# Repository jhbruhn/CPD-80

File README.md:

# Crazy Programmable Device (CPD)

## (Planned) Features

* 6MHz Z80 Processor
* UART Serial Communication
* 64k RAM
* 32k ROM
* CF Card Support (FAT16 or FAT12)

## Memory layout:
| Address       | Type |
| ------------- | ------------- |
| 0x0000-0x7FFF | ROM / RAM  |
| 0x8000-0xFFFF | RAM  |

## IO

| A11| A10| A9 | A8 | Device                                                  |
| ---|----|----|----|---------------------------------------------------------|
| 0  | 0  | 0  | 0  | IDE Port (CF Card)                                      |
| 0  | 0  | 0  | 1  | UART (16550)                                            |
| 0  | 0  | 1  | 0  | PS/2 Keyboard                                           |
| 0  | 0  | 1  | 1  | RTC-72421                                               |
| 0  | 1  | 0  | 0  | MemoryBank (write 0 for ROM and 2 for RAM in first 32k) |
| 0  | 1  | 0  | 1  | Video (TMS9918)                                         |
| 0  | 1  | 1  | 0  | Audio (AY-3-8910A)                                      |

To Address device 0:

B = 0

OUT (C), d

To Address device 1:

B = 1

OUT (C), d

etc...

sdcc:
__banked __ad(0x16c) int pedabaumert oder so

##Future:
Video Card with TMS9918. Also PS/2 keyboard input (or something similar). Real time Clock?

## Boot:
* start at 0x0000.
* load Bootsector from CF card to 0x8000, or into BANK RAM at 0x0000.
* jump to 0x8000 (0x0000)
* Bootsector loads FAT files, executes KERNEL.ULF or something like that. Autoexec.

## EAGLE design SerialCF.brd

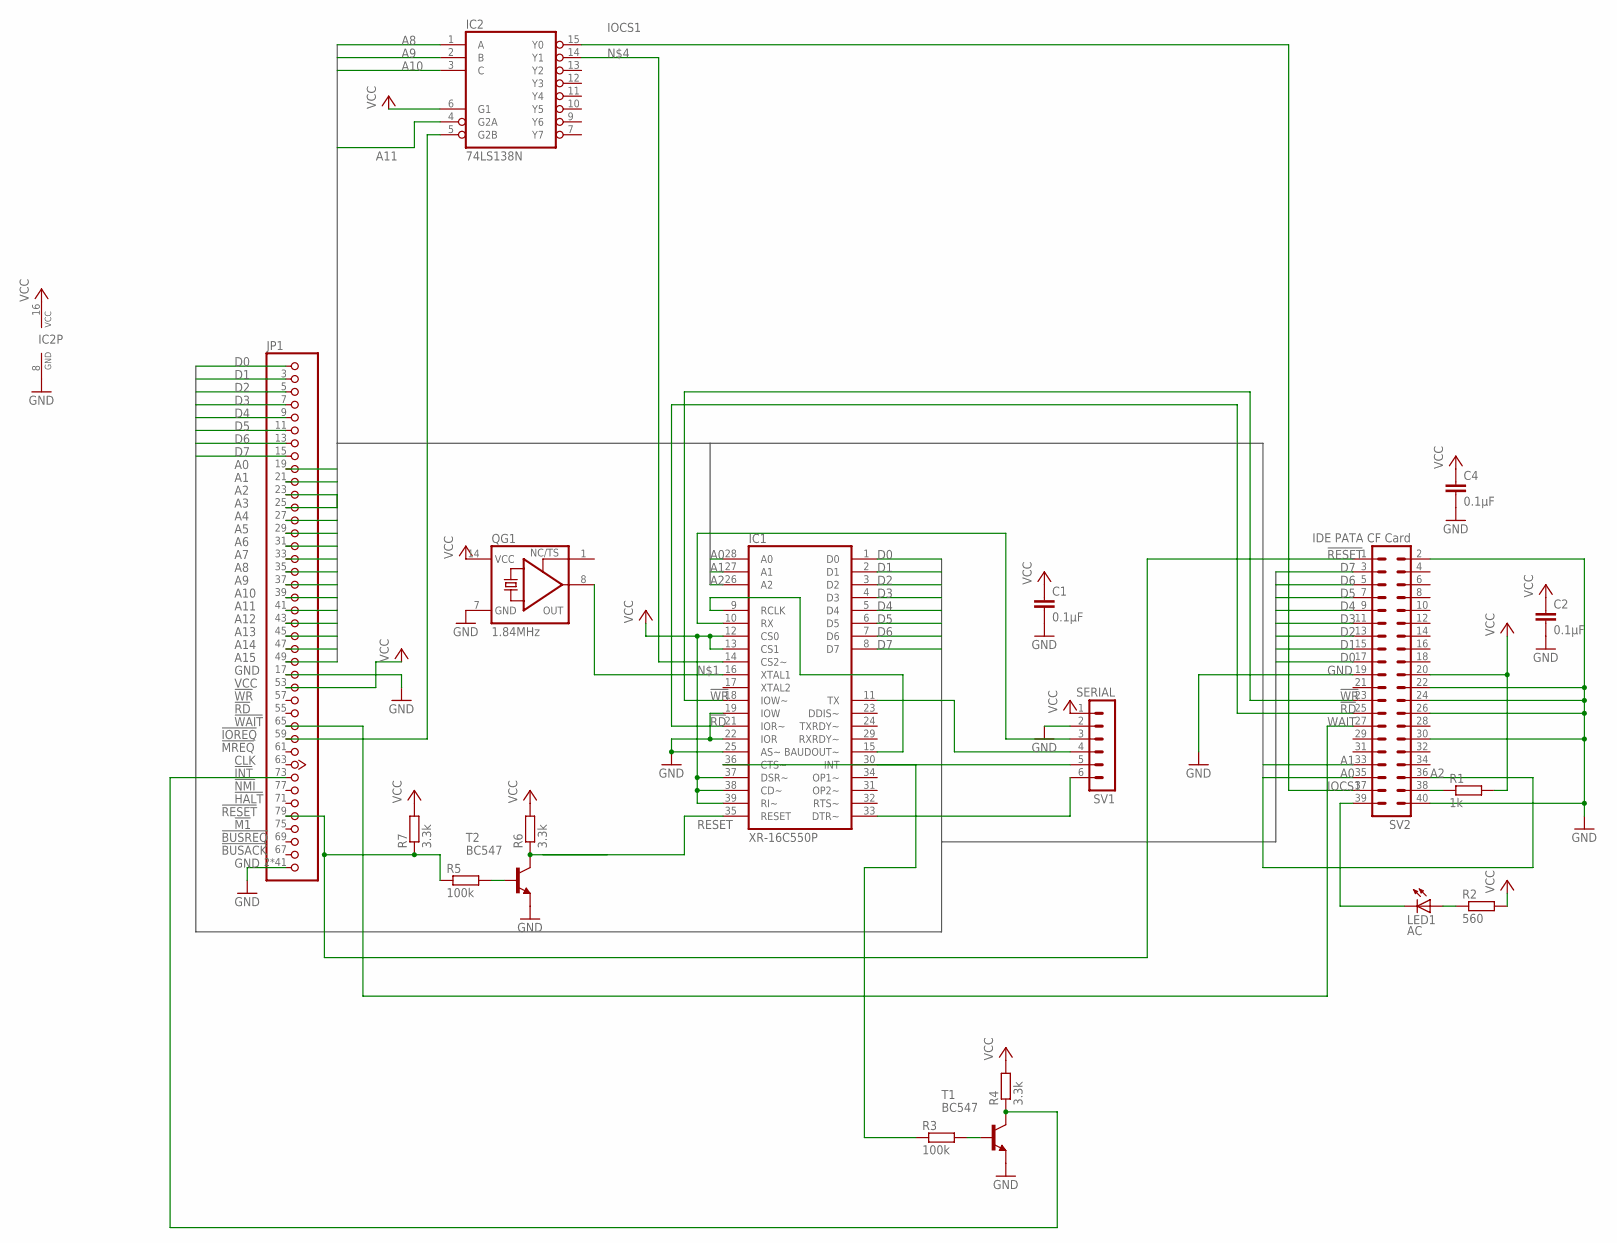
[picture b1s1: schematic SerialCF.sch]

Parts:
C1, C2, C4: 0.1µF; C5B2.5
IC1: XR-16C550P; DIL40
IC2: 74LS138N; DIL16
JP1: JEANNECTOR/90; 2X25/90
LED1: AC; LED5MM
QG1: 1.84MHz; DIL14S
R1: 1k; 0207/10; MPN MCRE000037
R2: 560; 0204/7
R3, R5: 100k; 0207/2V
R4, R6, R7: 3.3k; 0207/2V
SV1: SERIAL; MA06-1
SV2: IDE PATA CF Card; MA20-2
T1, T2: BC547; TO92

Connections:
!RD: IC1.21 (IOR~), SV2.25
!RESET: JP1.79 (!RESET), R7.1, SV2.1
!WR: IC1.18 (IOW~), SV2.23
A0: IC1.28 (A0), JP1.19 (A0), SV2.35
A1: IC1.27 (A1), JP1.21 (A1), SV2.33
A2: IC1.26 (A2), JP1.23 (A2), SV2.36
A3: JP1.25 (A3)
A4: JP1.27 (A4)
A5: JP1.29 (A5)
A6: JP1.31 (A6)
A7: JP1.33 (A7)
A8: IC2.1 (A), JP1.35 (A8)
A9: IC2.2 (B), JP1.37 (A9)
A10: IC2.3 (C), JP1.39 (A10)
A11: IC2.4 (G2A), JP1.41 (A11)
A12: JP1.43 (A12)
A13: JP1.45 (A13)
A14: JP1.47 (A14)
A15: JP1.49 (A15)
D0: IC1.1 (D0), JP1.1 (D0), SV2.17
D1: IC1.2 (D1), JP1.3 (D1), SV2.15
D2: IC1.3 (D2), JP1.5 (D2), SV2.13
D3: IC1.4 (D3), JP1.7 (D3), SV2.11
D4: IC1.5 (D4), JP1.9 (D4), SV2.9
D5: IC1.6 (D5), JP1.11 (D5), SV2.7
D6: IC1.7 (D6), JP1.13 (D6), SV2.5
D7: IC1.8 (D7), JP1.15 (D7), SV2.3
GND: C1.2, C2.2, C4.2, IC1.19 (IOW), IC1.20 (GND), IC1.22 (IOR), IC1.25 (AS~), IC2.8 (GND), JP1.2 (GND), JP1.4 (GND), JP1.6 (GND), JP1.8 (GND), JP1.10 (GND), JP1.12 (GND), JP1.14 (GND), JP1.16 (GND), JP1.17 (GND), JP1.18 (GND), JP1.20 (GND), JP1.22 (GND), JP1.24 (GND), JP1.26 (GND), JP1.28 (GND), JP1.30 (GND), JP1.32 (GND), JP1.34 (GND), JP1.36 (GND), JP1.38 (GND), JP1.40 (GND), JP1.42 (GND), JP1.44 (GND), JP1.46 (GND), JP1.48 (GND), JP1.50 (GND), JP1.51 (GND), JP1.52 (GND), JP1.54 (GND), JP1.56 (GND), JP1.58 (GND), JP1.60 (GND), JP1.62 (GND), JP1.64 (GND), JP1.66 (GND), JP1.68 (GND), JP1.70 (GND), JP1.72 (GND), JP1.74 (GND), JP1.76 (GND), JP1.78 (GND), JP1.80 (GND), QG1.7 (GND), SV1.2, SV2.2, SV2.19, SV2.22, SV2.24, SV2.26, SV2.30, SV2.40, T1.1 (E), T2.1 (E)
IOCS1: IC2.15 (Y0), SV2.37
unnamed: IC1.16 (XTAL1), QG1.8 (OUT)
unnamed: LED1.K (C), SV2.39
unnamed: LED1.A, R2.1
unnamed: IC1.14 (CS2~), IC2.14 (Y1)
unnamed: IC2.5 (G2B), JP1.59 (!IOREQ)
unnamed: R5.2, T2.2 (B)
unnamed: R6.1, T2.3 (C)
unnamed: R3.2, T1.2 (B)
unnamed: JP1.73 (!INT), R4.1, T1.3 (C)
unnamed: IC1.30 (INT), R3.1
unnamed: IC1.11 (TX), SV1.4
unnamed: IC1.36 (CTS~), SV1.5
unnamed: IC1.9 (RCLK), IC1.15 (BAUDOUT~)
unnamed: IC1.33 (DTR~), SV1.6
unnamed: IC1.10 (RX), SV1.3
unnamed: R1.1, SV2.38
RESET: IC1.35 (RESET)
VCC: C1.1, C2.1, C4.1, IC1.12 (CS0), IC1.13 (CS1), IC1.37 (DSR~), IC1.38 (CD~), IC1.39 (RI~), IC1.40 (VCC), IC2.6 (G1), IC2.16 (VCC), JP1.53 (VCC), QG1.14 (VCC), R1.2, R2.2, R4.2, R6.2, R7.2, SV1.1, SV2.20
WAIT: JP1.65 (!WAIT), SV2.27

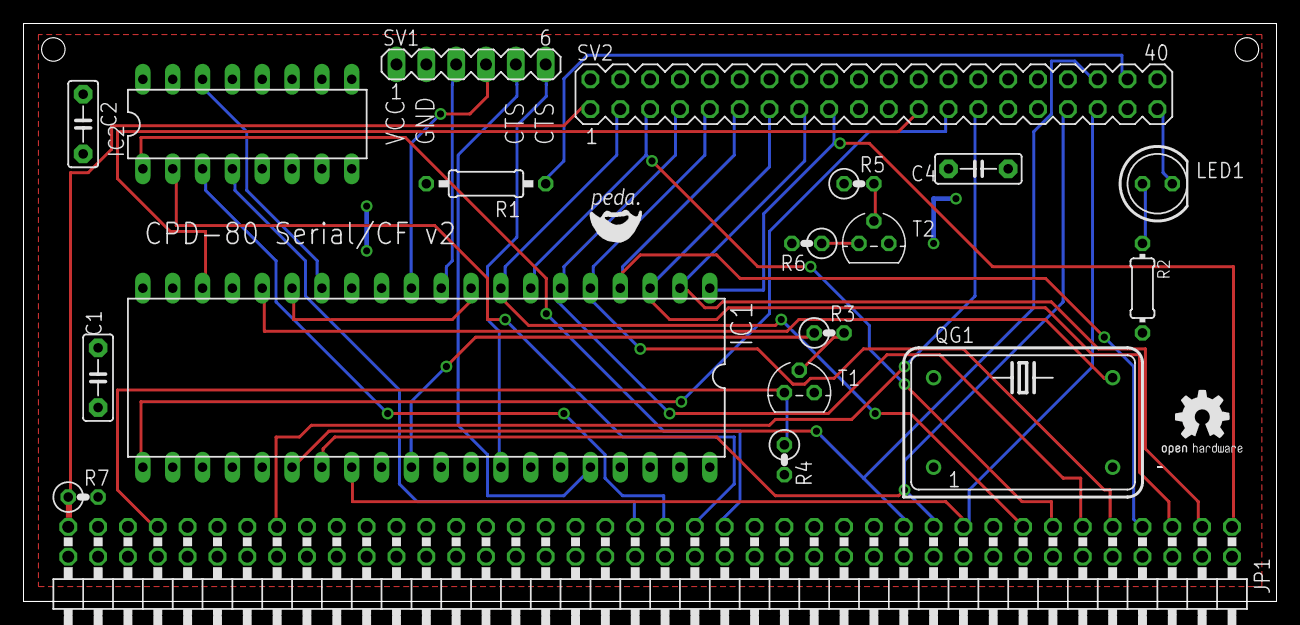
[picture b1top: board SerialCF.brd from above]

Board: 2 copper layers, 106.7 x 49.2 mm, 20 parts (0 on the bottom side), 38 nets.

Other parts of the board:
U$1: OSHW2

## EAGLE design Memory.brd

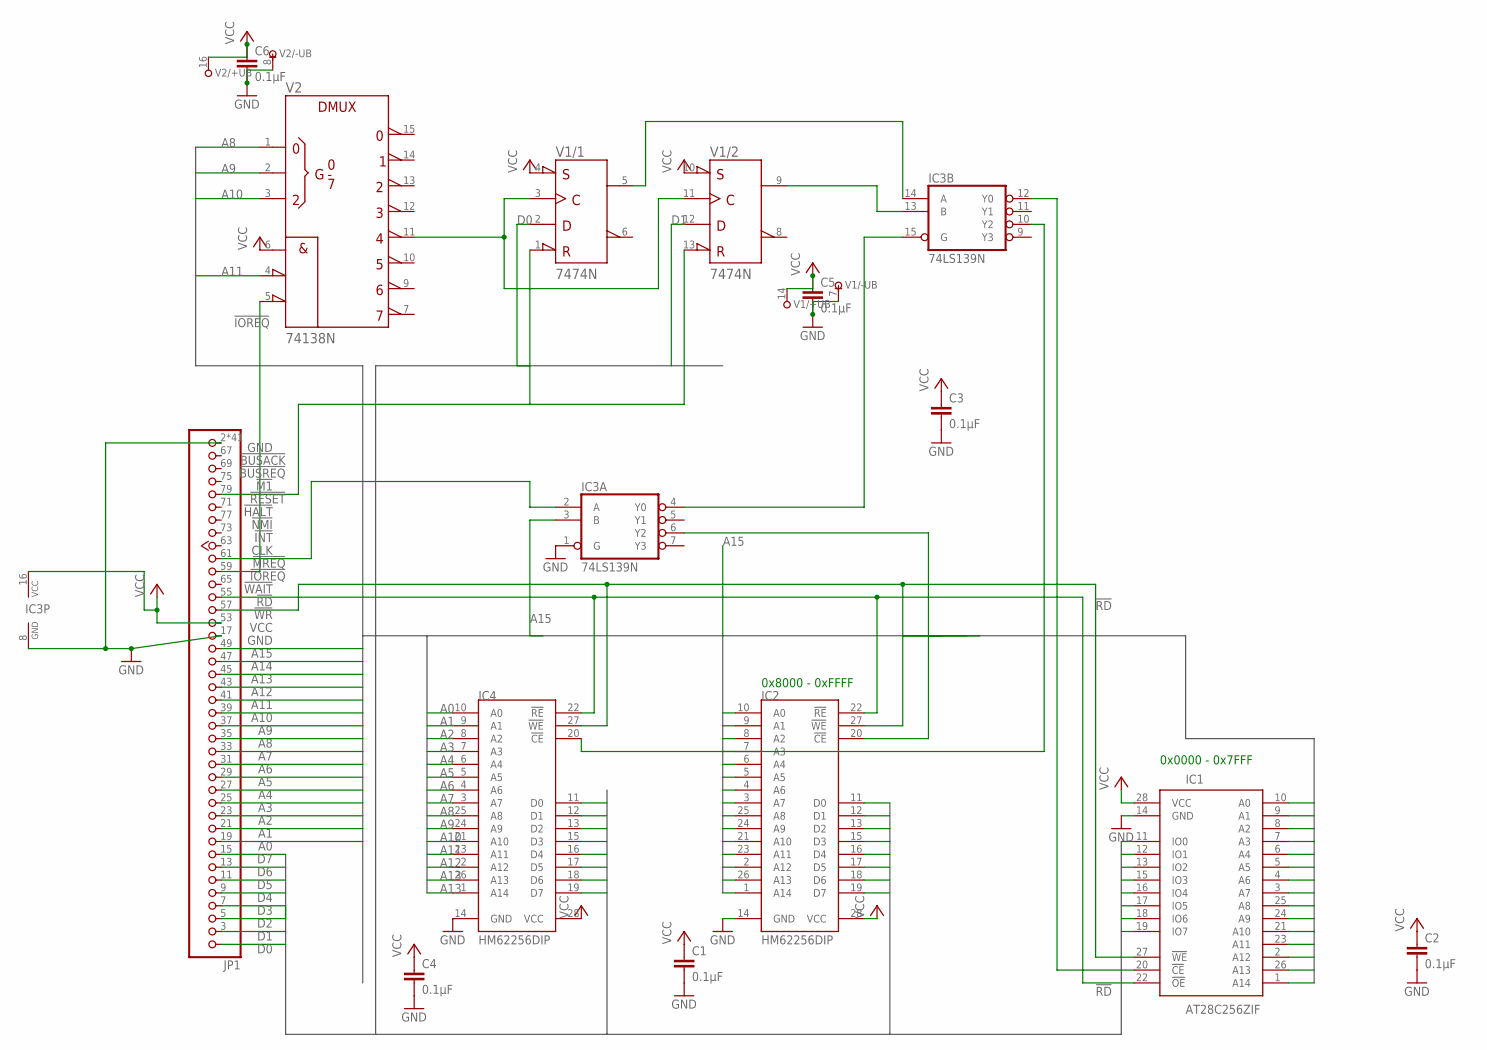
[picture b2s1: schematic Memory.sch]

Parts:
C1, C2, C3, C4, C5, C6: 0.1µF; C5B2.5
IC1: AT28C256ZIF; DIL28-ZIF
IC2, IC4: HM62256DIP; HM62256-DIP
IC3: 74LS139N; DIL16
JP1: JEANNECTOR/90; 2X25/90
V1: 7474N; DIL14
V2: 74138N; DIL16

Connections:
!IOREQ: JP1.59 (!IOREQ), V2.5 (!G2B)
!MREQ: IC3.2 (A), JP1.61 (!MREQ)
!RD: IC1.22 (!OE), IC2.22 (!RE), IC4.22 (!RE), JP1.55 (!RD)
!WR: IC1.27 (!WE), IC2.27 (!WE), IC4.27 (!WE), JP1.57 (!WR)
A0: IC1.10 (A0), IC2.10 (A0), IC4.10 (A0), JP1.19 (A0)
A1: IC1.9 (A1), IC2.9 (A1), IC4.9 (A1), JP1.21 (A1)
A2: IC1.8 (A2), IC2.8 (A2), IC4.8 (A2), JP1.23 (A2)
A3: IC1.7 (A3), IC2.7 (A3), IC4.7 (A3), JP1.25 (A3)
A4: IC1.6 (A4), IC2.6 (A4), IC4.6 (A4), JP1.27 (A4)
A5: IC1.5 (A5), IC2.5 (A5), IC4.5 (A5), JP1.29 (A5)
A6: IC1.4 (A6), IC2.4 (A6), IC4.4 (A6), JP1.31 (A6)
A7: IC1.3 (A7), IC2.3 (A7), IC4.3 (A7), JP1.33 (A7)
A8: IC1.25 (A8), IC2.25 (A8), IC4.25 (A8), JP1.35 (A8), V2.1 (A)
A9: IC1.24 (A9), IC2.24 (A9), IC4.24 (A9), JP1.37 (A9), V2.2 (B)
A10: IC1.21 (A10), IC2.21 (A10), IC4.21 (A10), JP1.39 (A10), V2.3 (C)
A11: IC1.23 (A11), IC2.23 (A11), IC4.23 (A11), JP1.41 (A11), V2.4 (!G2A)
A12: IC1.2 (A12), IC2.2 (A12), IC4.2 (A12), JP1.43 (A12)
A13: IC1.26 (A13), IC2.26 (A13), IC4.26 (A13), JP1.45 (A13)
A14: IC1.1 (A14), IC2.1 (A14), IC4.1 (A14), JP1.47 (A14)
A15: IC3.3 (B), JP1.49 (A15)
D0: IC1.11 (IO0), IC2.11 (D0), IC4.11 (D0), JP1.1 (D0), V1.2 (D)
D1: IC1.12 (IO1), IC2.12 (D1), IC4.12 (D1), JP1.3 (D1), V1.12 (D)
D2: IC1.13 (IO2), IC2.13 (D2), IC4.13 (D2), JP1.5 (D2)
D3: IC1.15 (IO3), IC2.15 (D3), IC4.15 (D3), JP1.7 (D3)
D4: IC1.16 (IO4), IC2.16 (D4), IC4.16 (D4), JP1.9 (D4)
D5: IC1.17 (IO5), IC2.17 (D5), IC4.17 (D5), JP1.11 (D5)
D6: IC1.18 (IO6), IC2.18 (D6), IC4.18 (D6), JP1.13 (D6)
D7: IC1.19 (IO7), IC2.19 (D7), IC4.19 (D7), JP1.15 (D7)
GND: C1.2, C2.2, C3.2, C4.2, C5.2, C6.2, IC1.14 (GND), IC2.14 (GND), IC3.1 (G), IC3.8 (GND), IC4.14 (GND), JP1.2 (GND), JP1.4 (GND), JP1.6 (GND), JP1.8 (GND), JP1.10 (GND), JP1.12 (GND), JP1.14 (GND), JP1.16 (GND), JP1.17 (GND), JP1.18 (GND), JP1.20 (GND), JP1.22 (GND), JP1.24 (GND), JP1.26 (GND), JP1.28 (GND), JP1.30 (GND), JP1.32 (GND), JP1.34 (GND), JP1.36 (GND), JP1.38 (GND), JP1.40 (GND), JP1.42 (GND), JP1.44 (GND), JP1.46 (GND), JP1.48 (GND), JP1.50 (GND), JP1.51 (GND), JP1.52 (GND), JP1.54 (GND), JP1.56 (GND), JP1.58 (GND), JP1.60 (GND), JP1.62 (GND), JP1.64 (GND), JP1.66 (GND), JP1.68 (GND), JP1.70 (GND), JP1.72 (GND), JP1.74 (GND), JP1.76 (GND), JP1.78 (GND), JP1.80 (GND), V1.7 (-UB), V2.8 (-UB)
unnamed: IC2.20 (!CE), IC3.6 (Y2)
unnamed: IC1.20 (!CE), IC3.12 (Y0)
unnamed: IC3.14 (A), V1.5 (Q)
unnamed: V1.3 (CLK), V1.11 (CLK), V2.11 (Y4)
unnamed: IC3.13 (B), V1.9 (Q)
unnamed: JP1.79 (!RESET), V1.1 (!CLR), V1.13 (!CLR)
unnamed: IC3.4 (Y0), IC3.15 (G)
unnamed: IC3.10 (Y2), IC4.20 (!CE)
VCC: C1.1, C2.1, C3.1, C4.1, C5.1, C6.1, IC1.28 (VCC), IC2.28 (VCC), IC3.16 (VCC), IC4.28 (VCC), JP1.53 (VCC), V1.4 (!PRE), V1.10 (!PRE), V1.14 (+UB), V2.6 (G1), V2.16 (+UB)

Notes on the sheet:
0x0000 - 0x7FFF
0x8000 - 0xFFFF

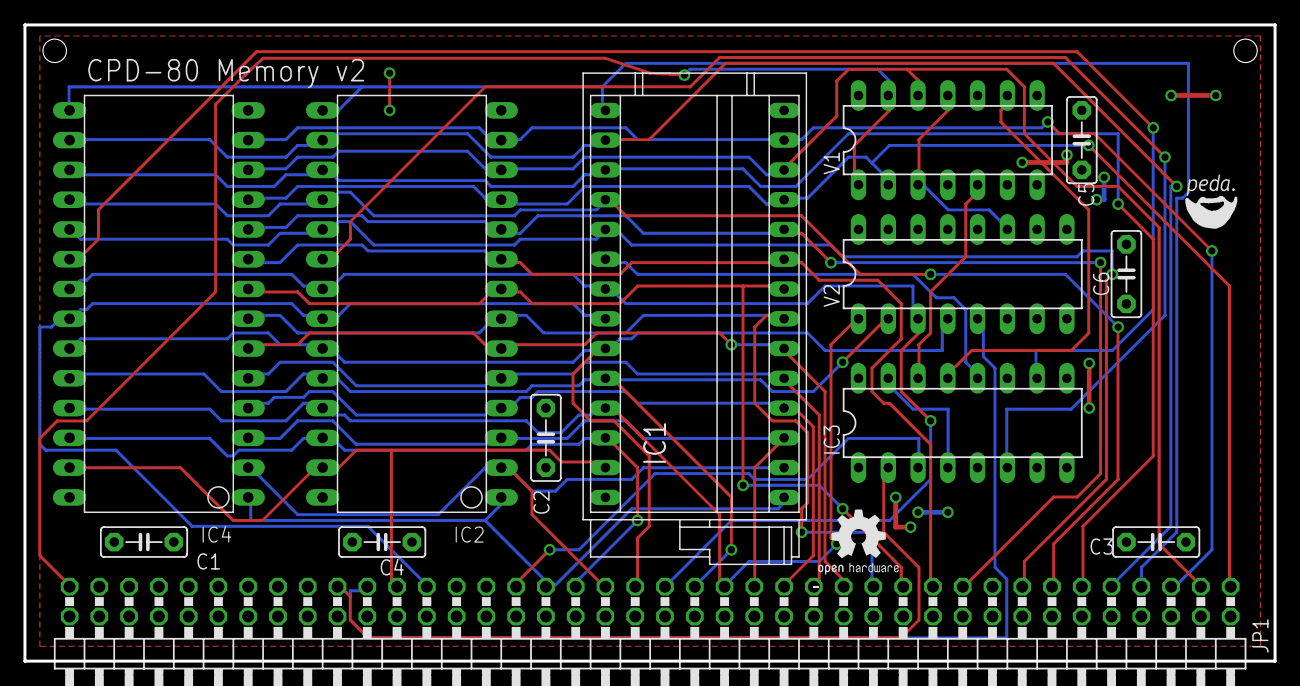
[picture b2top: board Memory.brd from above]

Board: 2 copper layers, 106.7 x 54.3 mm, 14 parts (0 on the bottom side), 38 nets.

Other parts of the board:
U$1: OSHW2

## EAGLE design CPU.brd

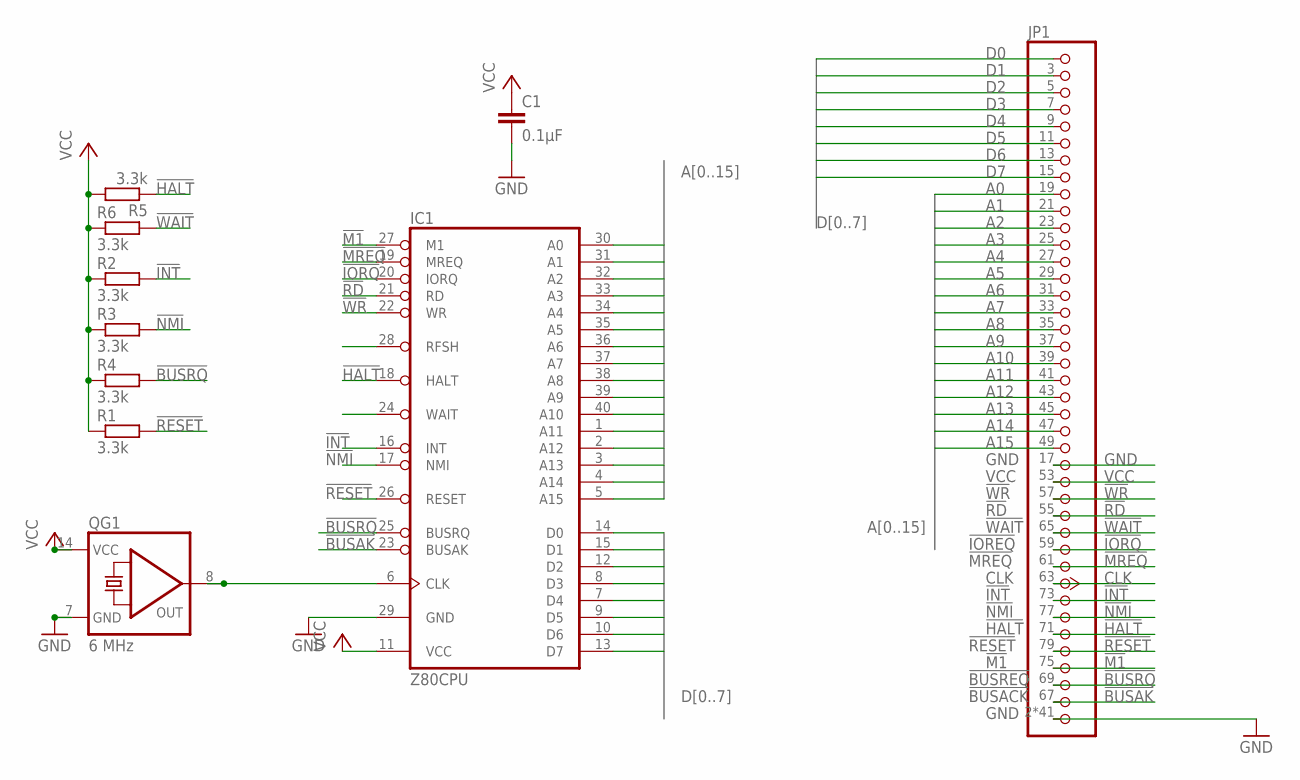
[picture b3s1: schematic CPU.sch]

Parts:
C1: 0.1µF; C5B2.5
IC1: Z80CPU; DIL40
JP1: JEANNECTOR/90; 2X25/90
QG1: 6 MHz; DIL14S
R1, R2, R3, R4, R5, R6: 3.3k; 0207/2V

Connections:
!BUSAK: IC1.23 (BUSAK), JP1.67 (!BUSACK)
!BUSRQ: IC1.25 (BUSRQ), JP1.69 (!BUSRQ), R4.2
!HALT: IC1.18 (HALT), JP1.71 (!HALT), R5.1
!INT: IC1.16 (INT), JP1.73 (!INT), R2.2
!IORQ: IC1.20 (IORQ), JP1.59 (!IOREQ)
!M1: IC1.27 (M1), JP1.75 (!M1)
!MREQ: IC1.19 (MREQ), JP1.61 (!MREQ)
!NMI: IC1.17 (NMI), JP1.77 (!NMI), R3.2
!RD: IC1.21 (RD), JP1.55 (!RD)
!RESET: IC1.26 (RESET), JP1.79 (!RESET), R1.2
!RFSH: IC1.28 (RFSH)
!WAIT: IC1.24 (WAIT), JP1.65 (!WAIT), R6.2
!WR: IC1.22 (WR), JP1.57 (!WR)
A0: IC1.30 (A0), JP1.19 (A0)
A1: IC1.31 (A1), JP1.21 (A1)
A2: IC1.32 (A2), JP1.23 (A2)
A3: IC1.33 (A3), JP1.25 (A3)
A4: IC1.34 (A4), JP1.27 (A4)
A5: IC1.35 (A5), JP1.29 (A5)
A6: IC1.36 (A6), JP1.31 (A6)
A7: IC1.37 (A7), JP1.33 (A7)
A8: IC1.38 (A8), JP1.35 (A8)
A9: IC1.39 (A9), JP1.37 (A9)
A10: IC1.40 (A10), JP1.39 (A10)
A11: IC1.1 (A11), JP1.41 (A11)
A12: IC1.2 (A12), JP1.43 (A12)
A13: IC1.3 (A13), JP1.45 (A13)
A14: IC1.4 (A14), JP1.47 (A14)
A15: IC1.5 (A15), JP1.49 (A15)
CLK: IC1.6 (CLK), JP1.63 (CLK), QG1.8 (OUT)
D0: IC1.14 (D0), JP1.1 (D0)
D1: IC1.15 (D1), JP1.3 (D1)
D2: IC1.12 (D2), JP1.5 (D2)
D3: IC1.8 (D3), JP1.7 (D3)
D4: IC1.7 (D4), JP1.9 (D4)
D5: IC1.9 (D5), JP1.11 (D5)
D6: IC1.10 (D6), JP1.13 (D6)
D7: IC1.13 (D7), JP1.15 (D7)
GND: C1.2, IC1.29 (GND), JP1.2 (GND), JP1.4 (GND), JP1.6 (GND), JP1.8 (GND), JP1.10 (GND), JP1.12 (GND), JP1.14 (GND), JP1.16 (GND), JP1.17 (GND), JP1.18 (GND), JP1.20 (GND), JP1.22 (GND), JP1.24 (GND), JP1.26 (GND), JP1.28 (GND), JP1.30 (GND), JP1.32 (GND), JP1.34 (GND), JP1.36 (GND), JP1.38 (GND), JP1.40 (GND), JP1.42 (GND), JP1.44 (GND), JP1.46 (GND), JP1.48 (GND), JP1.50 (GND), JP1.51 (GND), JP1.52 (GND), JP1.54 (GND), JP1.56 (GND), JP1.58 (GND), JP1.60 (GND), JP1.62 (GND), JP1.64 (GND), JP1.66 (GND), JP1.68 (GND), JP1.70 (GND), JP1.72 (GND), JP1.74 (GND), JP1.76 (GND), JP1.78 (GND), JP1.80 (GND), QG1.7 (GND)
VCC: C1.1, IC1.11 (VCC), JP1.53 (VCC), QG1.14 (VCC), R1.1, R2.1, R3.1, R4.1, R5.2, R6.1

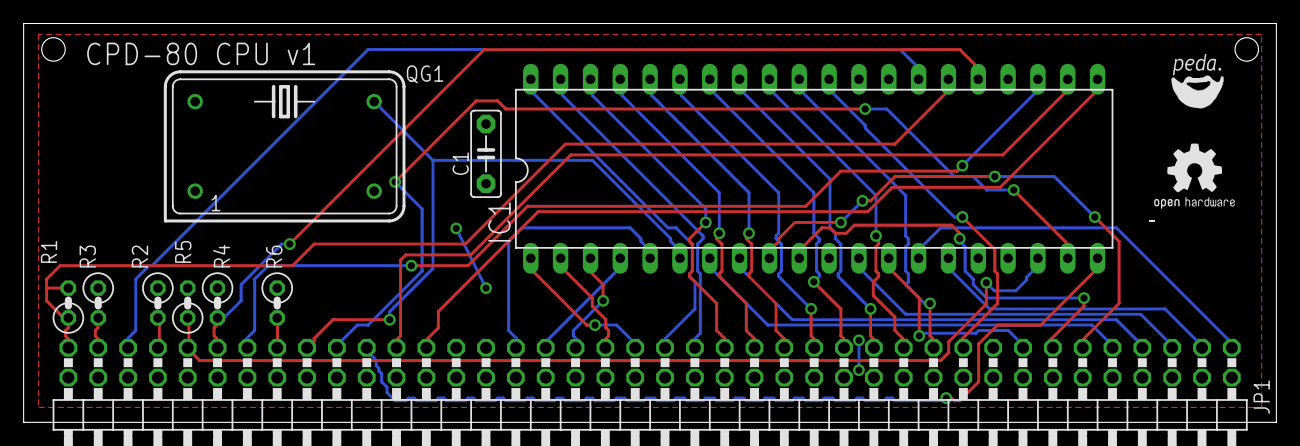
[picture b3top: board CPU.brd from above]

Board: 2 copper layers, 106.7 x 33.9 mm, 11 parts (0 on the bottom side), 39 nets.

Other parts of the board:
U$1: OSHW2

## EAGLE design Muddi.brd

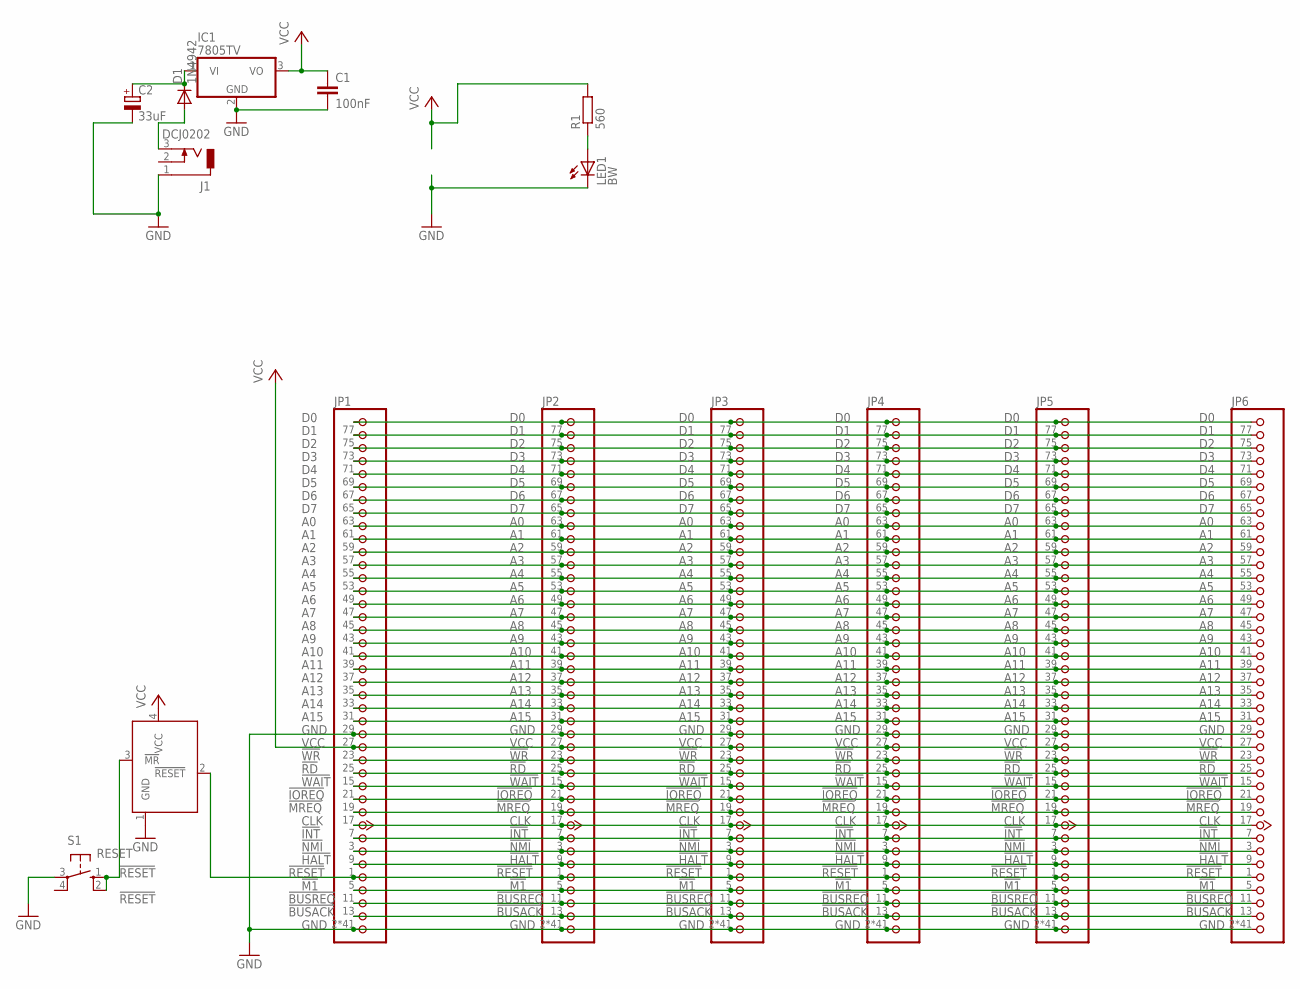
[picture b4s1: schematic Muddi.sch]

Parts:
C1: 100nF; C2.5-2
C2: 33uF; E2,5-7
D1: 1N4942; DO41-10; MPN 1N4935G
IC1: 7805TV; TO220V
J1: DCJ0202
JP1, JP2, JP3, JP4, JP5, JP6: JEANNECTOR_57102-F08-25; 57102-F08-25
LED1: BW; LED5MM
MAX811: MAX811; SOT143
R1: 560; 0207/2V
S1: RESET; B3F-10XX

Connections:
!BUSACK: JP1.13 (!BUSACK), JP2.13 (!BUSACK), JP3.13 (!BUSACK), JP4.13 (!BUSACK), JP5.13 (!BUSACK), JP6.13 (!BUSACK)
!BUSREQ: JP1.11 (!BUSRQ), JP2.11 (!BUSRQ), JP3.11 (!BUSRQ), JP4.11 (!BUSRQ), JP5.11 (!BUSRQ), JP6.11 (!BUSRQ)
!HALT: JP1.9 (!HALT), JP2.9 (!HALT), JP3.9 (!HALT), JP4.9 (!HALT), JP5.9 (!HALT), JP6.9 (!HALT)
!INT: JP1.7 (!INT), JP2.7 (!INT), JP3.7 (!INT), JP4.7 (!INT), JP5.7 (!INT), JP6.7 (!INT)
!IOREQ: JP1.21 (!IOREQ), JP2.21 (!IOREQ), JP3.21 (!IOREQ), JP4.21 (!IOREQ), JP5.21 (!IOREQ), JP6.21 (!IOREQ)
!M1: JP1.5 (!M1), JP2.5 (!M1), JP3.5 (!M1), JP4.5 (!M1), JP5.5 (!M1), JP6.5 (!M1)
!MREQ: JP1.19 (!MREQ), JP2.19 (!MREQ), JP3.19 (!MREQ), JP4.19 (!MREQ), JP5.19 (!MREQ), JP6.19 (!MREQ)
!NMI: JP1.3 (!NMI), JP2.3 (!NMI), JP3.3 (!NMI), JP4.3 (!NMI), JP5.3 (!NMI), JP6.3 (!NMI)
!RD: JP1.25 (!RD), JP2.25 (!RD), JP3.25 (!RD), JP4.25 (!RD), JP5.25 (!RD), JP6.25 (!RD)
!RESE: JP1.1 (!RESET), JP2.1 (!RESET), JP3.1 (!RESET), JP4.1 (!RESET), JP5.1 (!RESET), JP6.1 (!RESET), MAX811.2 (!RESET)
!WAIT: JP1.15 (!WAIT), JP2.15 (!WAIT), JP3.15 (!WAIT), JP4.15 (!WAIT), JP5.15 (!WAIT), JP6.15 (!WAIT)
!WR: JP1.23 (!WR), JP2.23 (!WR), JP3.23 (!WR), JP4.23 (!WR), JP5.23 (!WR), JP6.23 (!WR)
A0: JP1.63 (A0), JP2.63 (A0), JP3.63 (A0), JP4.63 (A0), JP5.63 (A0), JP6.63 (A0)
A15: JP1.31 (A15), JP2.31 (A15), JP3.31 (A15), JP4.31 (A15), JP5.31 (A15), JP6.31 (A15)
CLK: JP1.17 (CLK), JP2.17 (CLK), JP3.17 (CLK), JP4.17 (CLK), JP5.17 (CLK), JP6.17 (CLK)
D0: JP1.79 (D0), JP2.79 (D0), JP3.79 (D0), JP4.79 (D0), JP5.79 (D0), JP6.79 (D0)
D7: JP1.65 (D7), JP2.65 (D7), JP3.65 (D7), JP4.65 (D7), JP5.65 (D7), JP6.65 (D7)
GND: C1.2, C2.-, IC1.2 (GND), J1.1, JP1.2 (GND), JP1.4 (GND), JP1.6 (GND), JP1.8 (GND), JP1.10 (GND), JP1.12 (GND), JP1.14 (GND), JP1.16 (GND), JP1.18 (GND), JP1.20 (GND), JP1.22 (GND), JP1.24 (GND), JP1.26 (GND), JP1.28 (GND), JP1.29 (GND), JP1.30 (GND), JP1.32 (GND), JP1.34 (GND), JP1.36 (GND), JP1.38 (GND), JP1.40 (GND), JP1.42 (GND), JP1.44 (GND), JP1.46 (GND), JP1.48 (GND), JP1.50 (GND), JP1.51 (GND), JP1.52 (GND), JP1.54 (GND), JP1.56 (GND), JP1.58 (GND), JP1.60 (GND), JP1.62 (GND), JP1.64 (GND), JP1.66 (GND), JP1.68 (GND), JP1.70 (GND), JP1.72 (GND), JP1.74 (GND), JP1.76 (GND), JP1.78 (GND), JP1.80 (GND), JP2.2 (GND), JP2.4 (GND), JP2.6 (GND), JP2.8 (GND), JP2.10 (GND), JP2.12 (GND), JP2.14 (GND), JP2.16 (GND), JP2.18 (GND), JP2.20 (GND), JP2.22 (GND), JP2.24 (GND), JP2.26 (GND), JP2.28 (GND), JP2.29 (GND), JP2.30 (GND), JP2.32 (GND), JP2.34 (GND), JP2.36 (GND), JP2.38 (GND), JP2.40 (GND), JP2.42 (GND), JP2.44 (GND), JP2.46 (GND), JP2.48 (GND), JP2.50 (GND), JP2.51 (GND), JP2.52 (GND), JP2.54 (GND), JP2.56 (GND), JP2.58 (GND), JP2.60 (GND), JP2.62 (GND), JP2.64 (GND), JP2.66 (GND), JP2.68 (GND), JP2.70 (GND), JP2.72 (GND), JP2.74 (GND), JP2.76 (GND), JP2.78 (GND), JP2.80 (GND), JP3.2 (GND), JP3.4 (GND), JP3.6 (GND), JP3.8 (GND), JP3.10 (GND), JP3.12 (GND), JP3.14 (GND), JP3.16 (GND), JP3.18 (GND), JP3.20 (GND), JP3.22 (GND), JP3.24 (GND), JP3.26 (GND), JP3.28 (GND), JP3.29 (GND), JP3.30 (GND), JP3.32 (GND), JP3.34 (GND), JP3.36 (GND), JP3.38 (GND), JP3.40 (GND), JP3.42 (GND), JP3.44 (GND), JP3.46 (GND), JP3.48 (GND), JP3.50 (GND), JP3.51 (GND), JP3.52 (GND), JP3.54 (GND), JP3.56 (GND), JP3.58 (GND), JP3.60 (GND), JP3.62 (GND), JP3.64 (GND), JP3.66 (GND), JP3.68 (GND), JP3.70 (GND), JP3.72 (GND), JP3.74 (GND), JP3.76 (GND), JP3.78 (GND), JP3.80 (GND), JP4.2 (GND), JP4.4 (GND), JP4.6 (GND), JP4.8 (GND), JP4.10 (GND), JP4.12 (GND), JP4.14 (GND), JP4.16 (GND), JP4.18 (GND), JP4.20 (GND), JP4.22 (GND), JP4.24 (GND), JP4.26 (GND), JP4.28 (GND), JP4.29 (GND), JP4.30 (GND), JP4.32 (GND), JP4.34 (GND), JP4.36 (GND), JP4.38 (GND), JP4.40 (GND), JP4.42 (GND), JP4.44 (GND), JP4.46 (GND), JP4.48 (GND), JP4.50 (GND), JP4.51 (GND), JP4.52 (GND), JP4.54 (GND), JP4.56 (GND), JP4.58 (GND), JP4.60 (GND), JP4.62 (GND), JP4.64 (GND), JP4.66 (GND), JP4.68 (GND), JP4.70 (GND), JP4.72 (GND), JP4.74 (GND), JP4.76 (GND), JP4.78 (GND), JP4.80 (GND), JP5.2 (GND), JP5.4 (GND), JP5.6 (GND), JP5.8 (GND), JP5.10 (GND), JP5.12 (GND), JP5.14 (GND), JP5.16 (GND), JP5.18 (GND), JP5.20 (GND), JP5.22 (GND), JP5.24 (GND), JP5.26 (GND), JP5.28 (GND), JP5.29 (GND), JP5.30 (GND), JP5.32 (GND), JP5.34 (GND), JP5.36 (GND), JP5.38 (GND), JP5.40 (GND), JP5.42 (GND), JP5.44 (GND), JP5.46 (GND), JP5.48 (GND), JP5.50 (GND), JP5.51 (GND), JP5.52 (GND), JP5.54 (GND), JP5.56 (GND), JP5.58 (GND), JP5.60 (GND), JP5.62 (GND), JP5.64 (GND), JP5.66 (GND), JP5.68 (GND), JP5.70 (GND), JP5.72 (GND), JP5.74 (GND), JP5.76 (GND), JP5.78 (GND), JP5.80 (GND), JP6.2 (GND), JP6.4 (GND), JP6.6 (GND), JP6.8 (GND), JP6.10 (GND), JP6.12 (GND), JP6.14 (GND), JP6.16 (GND), JP6.18 (GND), JP6.20 (GND), JP6.22 (GND), JP6.24 (GND), JP6.26 (GND), JP6.28 (GND), JP6.29 (GND), JP6.30 (GND), JP6.32 (GND), JP6.34 (GND), JP6.36 (GND), JP6.38 (GND), JP6.40 (GND), JP6.42 (GND), JP6.44 (GND), JP6.46 (GND), JP6.48 (GND), JP6.50 (GND), JP6.51 (GND), JP6.52 (GND), JP6.54 (GND), JP6.56 (GND), JP6.58 (GND), JP6.60 (GND), JP6.62 (GND), JP6.64 (GND), JP6.66 (GND), JP6.68 (GND), JP6.70 (GND), JP6.72 (GND), JP6.74 (GND), JP6.76 (GND), JP6.78 (GND), JP6.80 (GND), LED1.K (C), MAX811.1 (GND), S1.3
unnamed: D1.A, J1.3
unnamed: JP1.77 (D1), JP2.77 (D1), JP3.77 (D1), JP4.77 (D1), JP5.77 (D1), JP6.77 (D1)
unnamed: JP1.75 (D2), JP2.75 (D2), JP3.75 (D2), JP4.75 (D2), JP5.75 (D2), JP6.75 (D2)
unnamed: JP1.73 (D3), JP2.73 (D3), JP3.73 (D3), JP4.73 (D3), JP5.73 (D3), JP6.73 (D3)
unnamed: JP1.71 (D4), JP2.71 (D4), JP3.71 (D4), JP4.71 (D4), JP5.71 (D4), JP6.71 (D4)
unnamed: JP1.69 (D5), JP2.69 (D5), JP3.69 (D5), JP4.69 (D5), JP5.69 (D5), JP6.69 (D5)
unnamed: JP1.67 (D6), JP2.67 (D6), JP3.67 (D6), JP4.67 (D6), JP5.67 (D6), JP6.67 (D6)
unnamed: JP1.61 (A1), JP2.61 (A1), JP3.61 (A1), JP4.61 (A1), JP5.61 (A1), JP6.61 (A1)
unnamed: JP1.59 (A2), JP2.59 (A2), JP3.59 (A2), JP4.59 (A2), JP5.59 (A2), JP6.59 (A2)
unnamed: JP1.57 (A3), JP2.57 (A3), JP3.57 (A3), JP4.57 (A3), JP5.57 (A3), JP6.57 (A3)
unnamed: JP1.55 (A4), JP2.55 (A4), JP3.55 (A4), JP4.55 (A4), JP5.55 (A4), JP6.55 (A4)
unnamed: JP1.53 (A5), JP2.53 (A5), JP3.53 (A5), JP4.53 (A5), JP5.53 (A5), JP6.53 (A5)
unnamed: JP1.49 (A6), JP2.49 (A6), JP3.49 (A6), JP4.49 (A6), JP5.49 (A6), JP6.49 (A6)
unnamed: JP1.47 (A7), JP2.47 (A7), JP3.47 (A7), JP4.47 (A7), JP5.47 (A7), JP6.47 (A7)
unnamed: JP1.45 (A8), JP2.45 (A8), JP3.45 (A8), JP4.45 (A8), JP5.45 (A8), JP6.45 (A8)
unnamed: JP1.43 (A9), JP2.43 (A9), JP3.43 (A9), JP4.43 (A9), JP5.43 (A9), JP6.43 (A9)
unnamed: JP1.41 (A10), JP2.41 (A10), JP3.41 (A10), JP4.41 (A10), JP5.41 (A10), JP6.41 (A10)
unnamed: JP1.39 (A11), JP2.39 (A11), JP3.39 (A11), JP4.39 (A11), JP5.39 (A11), JP6.39 (A11)
unnamed: JP1.37 (A12), JP2.37 (A12), JP3.37 (A12), JP4.37 (A12), JP5.37 (A12), JP6.37 (A12)
unnamed: JP1.35 (A13), JP2.35 (A13), JP3.35 (A13), JP4.35 (A13), JP5.35 (A13), JP6.35 (A13)
unnamed: JP1.33 (A14), JP2.33 (A14), JP3.33 (A14), JP4.33 (A14), JP5.33 (A14), JP6.33 (A14)
unnamed: LED1.A, R1.1
unnamed: C2.+, D1.C, IC1.1 (VI)
unnamed: MAX811.3 (!MR), S1.1 (S), S1.2 (S1)
VCC: C1.1, IC1.3 (VO), JP1.27 (VCC), JP2.27 (VCC), JP3.27 (VCC), JP4.27 (VCC), JP5.27 (VCC), JP6.27 (VCC), MAX811.4 (VCC), R1.2

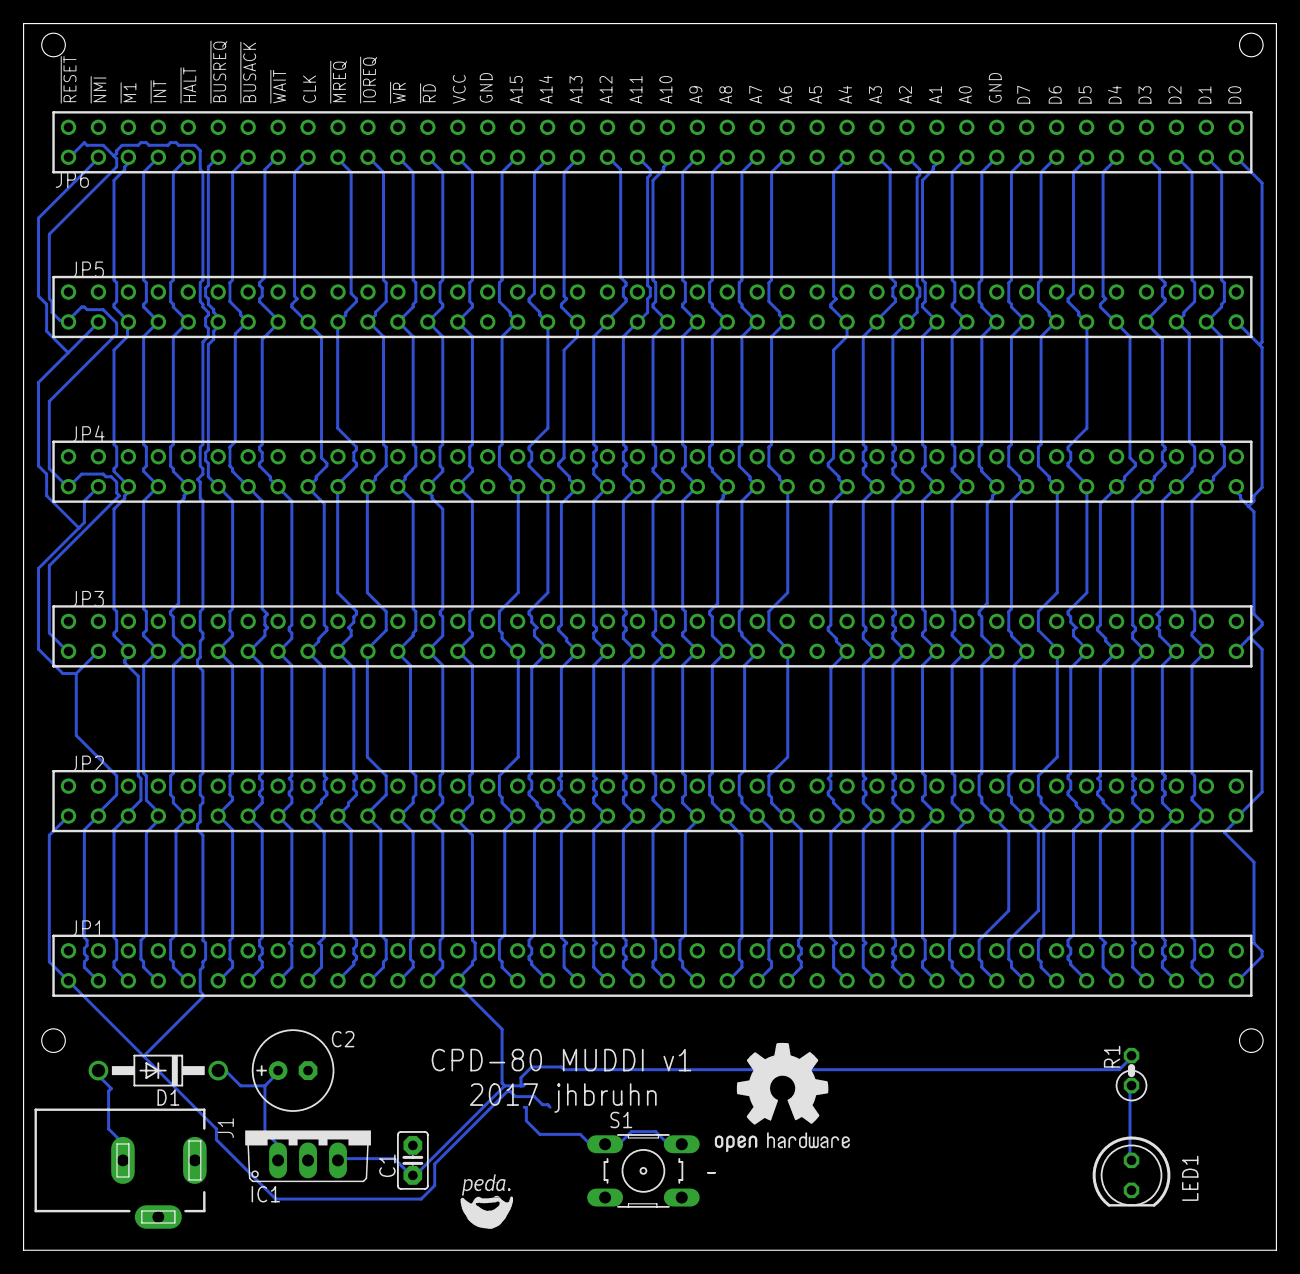
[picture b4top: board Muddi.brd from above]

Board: 2 copper layers, 106.3 x 104.0 mm, 16 parts (1 on the bottom side), 43 nets.

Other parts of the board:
U$1: OSHW1
